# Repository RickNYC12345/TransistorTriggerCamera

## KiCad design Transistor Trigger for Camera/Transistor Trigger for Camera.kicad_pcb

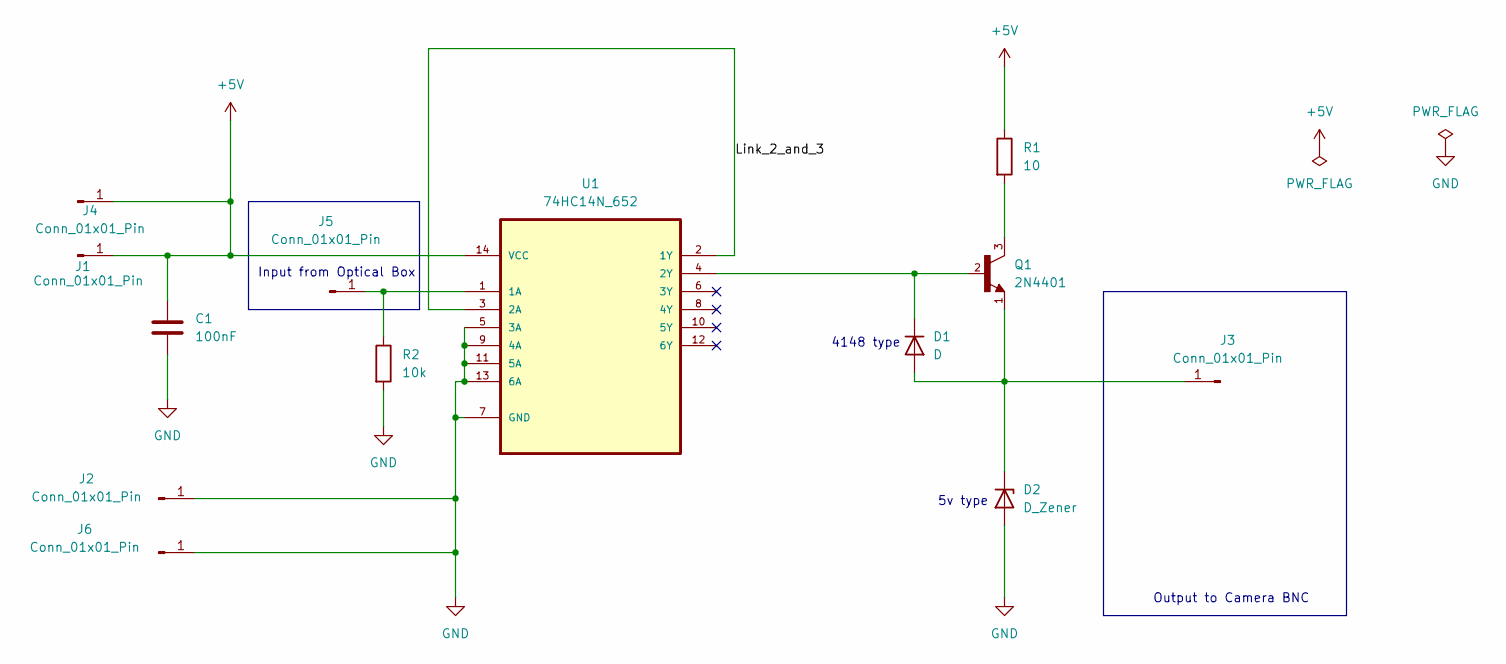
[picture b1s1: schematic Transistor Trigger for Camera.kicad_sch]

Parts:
C1: 100nF; CP_Radial_D8.0mm_P5.00mm
D1: D; D_T-1_P10.16mm_Horizontal
D2: D_Zener; D_T-1_P10.16mm_Horizontal
J1, J2, J3, J4, J5, J6: Conn_01x01_Pin; TE_MATE-N-LOK_1-794374-x_1x01_P4.14mm_Horizontal
Q1: 2N4401; TO92
R1: 10; R_Axial_DIN0207_L6.3mm_D2.5mm_P15.24mm_Horizontal
R2: 10k; R_Axial_DIN0207_L6.3mm_D2.5mm_P15.24mm_Horizontal
U1: 74HC14N_652; DIP254P762X420-14; MPN 74HC14N,652

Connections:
+5V: C1.1, J1.1, J4.1, R1.1, U1.14 (VCC)
/Link_2_and_3: U1.2 (1Y), U1.3 (2A)
GND: C1.2, D2.2 (A), J2.1, J6.1, R2.2, U1.5 (3A), U1.7 (GND), U1.9 (4A), U1.11 (5A), U1.13 (6A)
unnamed: D1.2 (A), D2.1 (K), J3.1, Q1.1
unnamed: D1.1 (K), Q1.2, U1.4 (2Y)
unnamed: J5.1, R2.1, U1.1 (1A)
unnamed: Q1.3, R1.2

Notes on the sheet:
5v type
Input from Optical Box
Output to Camera BNC
4148 type

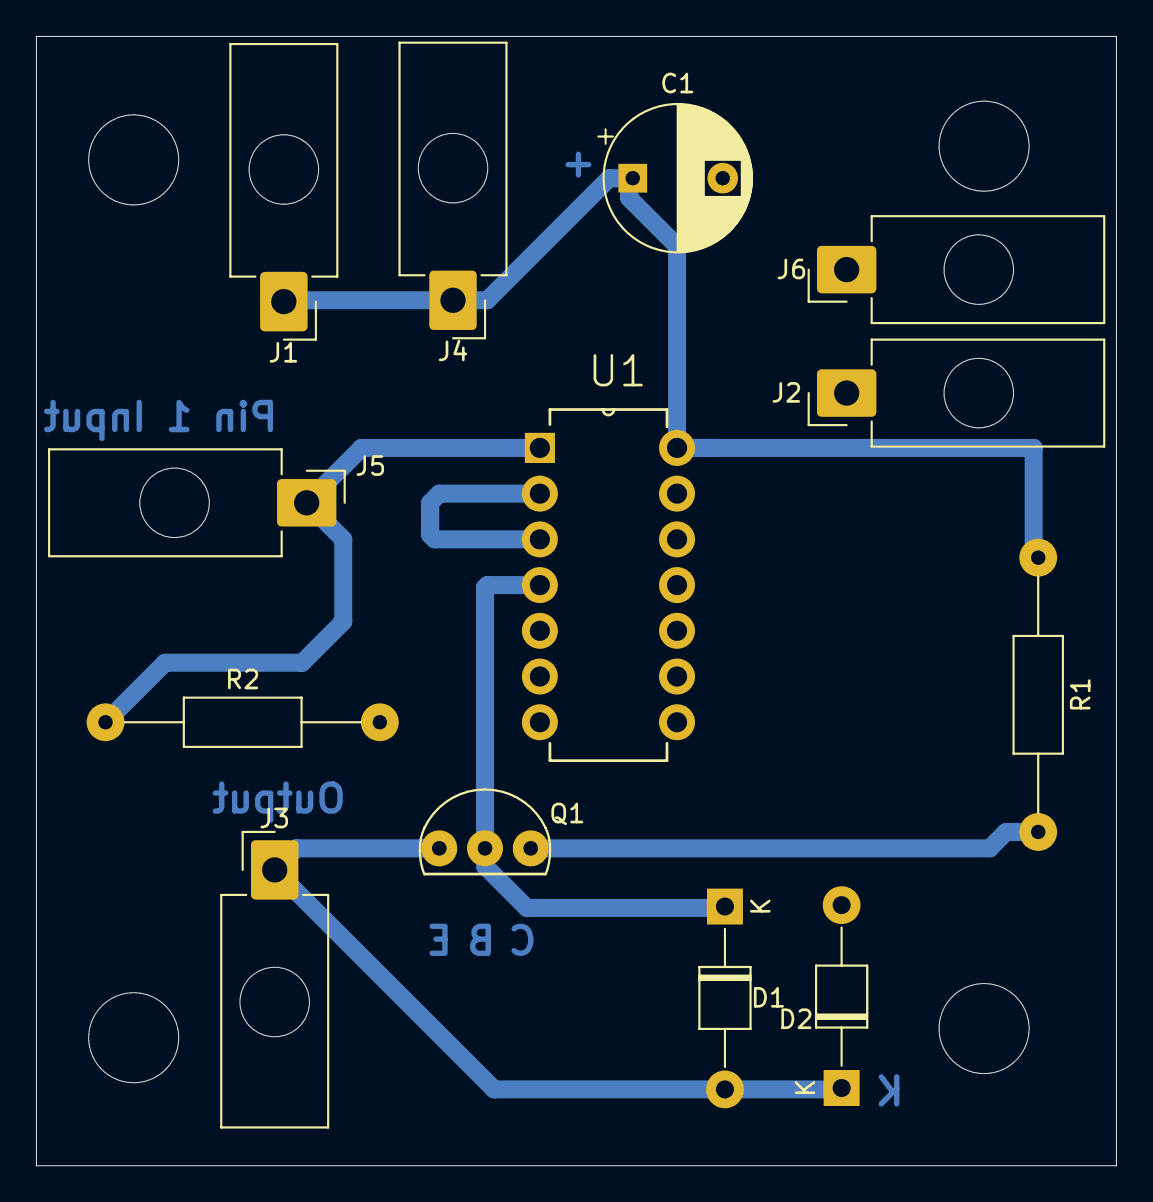
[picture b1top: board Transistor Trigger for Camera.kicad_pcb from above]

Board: 2 copper layers, 60.0 x 62.7 mm, 13 parts (0 on the bottom side), 7 nets.

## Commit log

2025-02-13 second update with new 100k resistor
2025-02-13 third update with Mark and parts
2025-02-17 Final revistion changes for layout
2025-02-18 further changes to layout
